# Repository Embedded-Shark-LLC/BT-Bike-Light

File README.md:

# BT-Bike-Light
Bluetooth-enabled bike light

## Hardware architecture diagram

## PCB Renders
|PCB Front|PCB Back|
|---------|--------|
|||

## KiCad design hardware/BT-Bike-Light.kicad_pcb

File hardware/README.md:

# Hardware

## Architecture diagram

## Major components
| Description           | Part Number           | Manufacturer          | Comments                          |
| --------------------- | --------------------- | --------------------- | --------------------------------- |
| Bluetooth module      | BT832                 | Fanstel               | 1.7-3.6 V, nRF52832               |
| Battery management IC | nPM1300               | Nordic Semiconductor  | 800 mA charge, onboard buck/LDO   |
| 24 GHz Radar module   | FEM11-F09             | Terasilic             | (not yet tested)                  |
| LED driver            | TPS92201              | Texas Instruments     | 2.5-5.5 V, 1.5 A                  |
| USB C port            | UJC-HP2-3-SMT-TR      | CUI Devices           | Power only, horizontal            |
| Red LED               | XPEBRD-L1-0000-00901  | Cree                  | 1.5 A, ~2.65 V @ 1.5 A            |
| Interface button      | PTS645VM31-2 LFS      | C&K                   | Right angle, THT                  |
| Buzzer                | SMT-0827-S-HT-R       | PUI Audio             | 2-5 V, 2.7 kHz, 85 dB @ 3.6V      |

## Minor components
| Description           | Part Number           | Manufacturer          | Comments                          |
| --------------------- | --------------------- | --------------------- | --------------------------------- |
| Fuse                  | TR/0603FA5-R          | Eaton                 | 5A rating, 35A breaking capacity  |
| Buzzer NMOS FET       | DMN3731U-7            | Diodes Incorporated   | Vgs < 1.8 V                       |
| 2.2 uH inductor (nPM) | WLFM201209M2R2PC      | Walson Technology     | 170 mR DCR, 0805                  |
| 2.2 uH inductor (LED) | SDER041H-2R2MS        | Cyntek                | 3.1A, 45mR DCR                    |

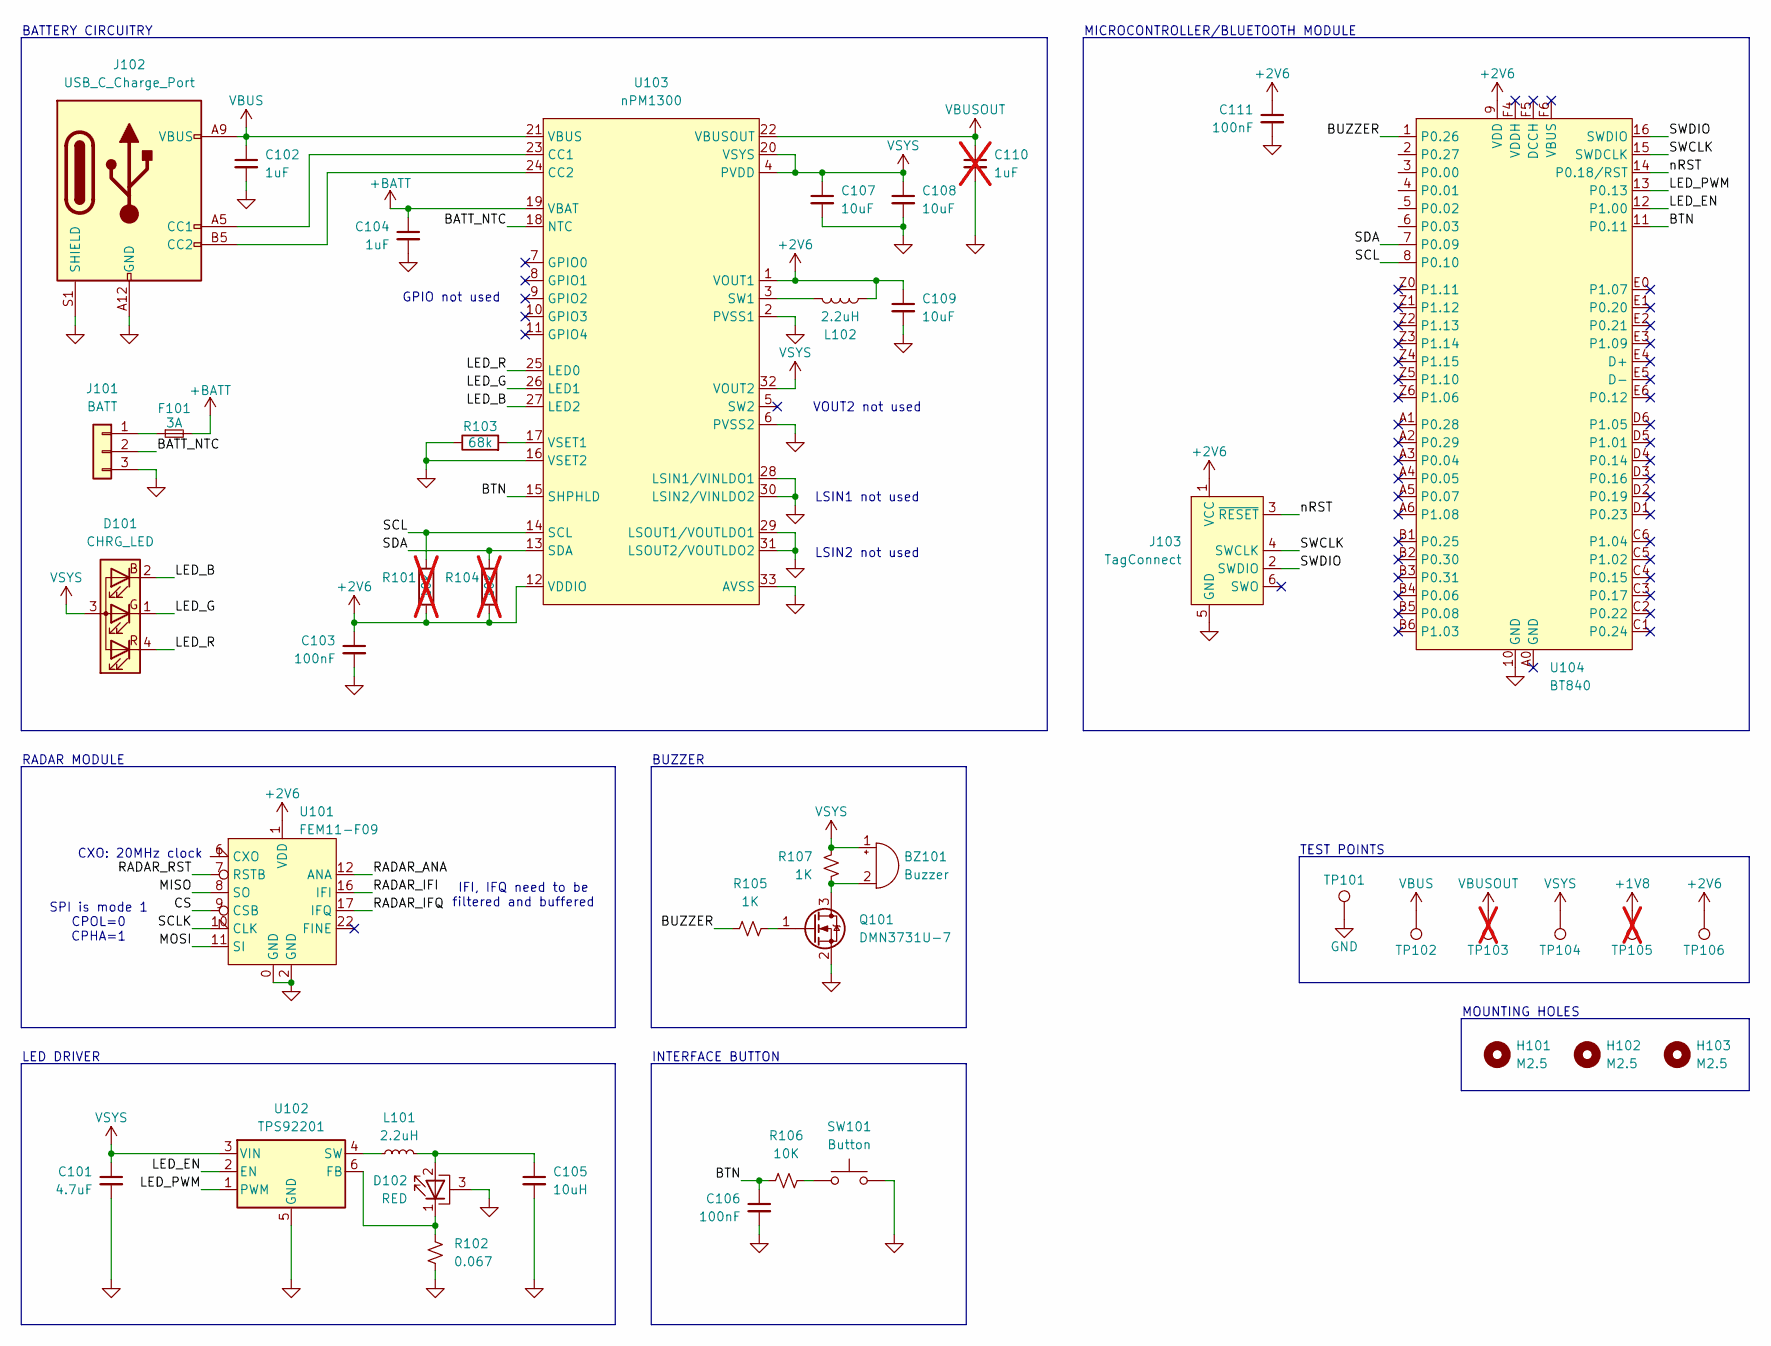
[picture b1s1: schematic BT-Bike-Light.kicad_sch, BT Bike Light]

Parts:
BZ101: Buzzer; SMT-0827-S-HT-R
C101: 4.7uF; C_0805_2012Metric_Pad1.18x1.45mm_HandSolder
C102, C104: 1uF; C_0805_2012Metric_Pad1.18x1.45mm_HandSolder
C103, C106, C111: 100nF; C_0805_2012Metric_Pad1.18x1.45mm_HandSolder
C105: 10uH; C_0805_2012Metric_Pad1.18x1.45mm_HandSolder
C107, C108, C109: 10uF; C_0805_2012Metric_Pad1.18x1.45mm_HandSolder
C110: 1uF; C_0805_2012Metric_Pad1.18x1.45mm_HandSolder; not fitted
D101: CHRG_LED; LED_0606
D102: RED; LED_Cree-XP
F101: 3A; Fuse_0603_1608Metric
H101, H102, H103: M2.5; MountingHole_2.7mm_M2.5
J101: BATT; JST_SH_SM03B-SRSS-TB_1x03-1MP_P1.00mm_Horizontal
J102: USB_C_Charge_Port; UJC-HP2-3-SMT-TR
J103: TagConnect; Tag-Connect_TC2030-IDC-NL_2x03_P1.27mm_Vertical
L101: 2.2uH; Inductor_3.6x4.1
L102: 2.2uH; L_0805_2012Metric
Q101: DMN3731U-7; SOT-23
R101, R104: 10k; R_0805_2012Metric_Pad1.20x1.40mm_HandSolder; not fitted
R102: 0.067; R_0805_2012Metric_Pad1.20x1.40mm_HandSolder
R103: 68k; R_0805_2012Metric_Pad1.20x1.40mm_HandSolder
R105, R107: 1K; R_0805_2012Metric_Pad1.20x1.40mm_HandSolder
R106: 10K; R_0805_2012Metric_Pad1.20x1.40mm_HandSolder
SW101: Button; SW_Tactile_SPST_Angled_PTS645Vx31-2LFS
TP101: GND; TestPoint_Pad_2.0x2.0mm
TP102: VBUS; TestPoint_Pad_2.0x2.0mm
TP103: VBUSOUT; TestPoint_Pad_2.0x2.0mm; not fitted
TP104: VSYS; TestPoint_Pad_2.0x2.0mm
TP105: 1V8; TestPoint_Pad_2.0x2.0mm; not fitted
TP106: 2V6; TestPoint_Pad_2.0x2.0mm
U101: FEM11-F09
U102: TPS92201; WSON-6-1EP_2x2mm_P0.65mm_EP1x1.6mm_ThermalVias
U103: nPM1300; QFN-32-1EP_5x5mm_P0.5mm_EP3.45x3.45mm_ThermalVias
U104: BT840

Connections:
+2V6: C103.1, C109.1, C111.1, J103.1 (VCC), L102.2, R101.2, R104.2, TP106.1, U101.1 (VDD), U101.14 (VDD), U101.19 (VDD), U103.1 (VOUT1), U103.12 (VDDIO), U104.9 (VDD)
+BATT: C104.1, F101.2, U103.19 (VBAT)
/BATT_NTC: J101.2, U103.18 (NTC)
/BTN: C106.1, R106.1, U103.15 (SHPHLD), U104.11 (P0.11)
/BUZZER: R105.1, U104.1 (P0.26)
/CS: U101.9 (CSB)
/LED_B: D101.2 (BK), U103.27 (LED2)
/LED_EN: U102.2 (EN), U104.12 (P1.00)
/LED_G: D101.1 (GK), U103.26 (LED1)
/LED_PWM: U102.1 (PWM), U104.13 (P0.13)
/LED_R: D101.4 (RK), U103.25 (LED0)
/MISO: U101.8 (SO)
/MOSI: U101.11 (SI)
/RADAR_ANA: U101.12 (ANA)
/RADAR_IFI: U101.16 (IFI)
/RADAR_IFQ: U101.17 (IFQ)
/RADAR_RST: U101.7 (RSTB)
/SCL: R101.1, U103.14 (SCL), U104.8 (P0.10)
/SCLK: U101.10 (CLK)
/SDA: R104.1, U103.13 (SDA), U104.7 (P0.09)
/SWCLK: J103.4 (SWCLK), U104.15 (SWDCLK)
/SWDIO: J103.2 (SWDIO), U104.16 (SWDIO)
/nRST: J103.3 (~RESET), U104.14 (P0.18/RST)
unnamed: BZ101.2 (-), Q101.3 (D), R107.2
unnamed: C105.1, D102.2 (A), L101.2
unnamed: D102.1 (K), R102.2, U102.6 (FB)
unnamed: F101.1, J101.1
unnamed: J102.A5 (CC1), U103.23 (CC1)
unnamed: J102.B5 (CC2), U103.24 (CC2)
unnamed: Q101.1 (G), R105.2
unnamed: R106.2, SW101.2
unnamed: L101.1, U102.4 (SW)
unnamed: L102.1, U103.3 (SW1)
unnamed: R103.2, U103.17 (VSET1)
VBUS: C102.1, J102.A9 (VBUS), J102.B9 (VBUS), TP102.1, U103.21 (VBUS)
VBUSOUT: C110.1, TP103.1, U103.22 (VBUSOUT)
VSYS: BZ101.1 (+), C101.1, C107.1, C108.1, D101.3 (A), R107.1, TP104.1, U102.3 (VIN), U103.4 (PVDD), U103.20 (VSYS), U103.32 (VOUT2)

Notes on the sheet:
CXO: 20MHz clock
LSIN1 not used
INTERFACE BUTTON
MOUNTING HOLES
TEST POINTS
GPIO not used
IFI, IFQ need to be filtered and buffered
BATTERY CIRCUITRY
BUZZER
VOUT2 not used
LSIN2 not used
RADAR MODULE
MICROCONTROLLER/BLUETOOTH MODULE
LED DRIVER
SPI is mode 1 CPOL=0 CPHA=1

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
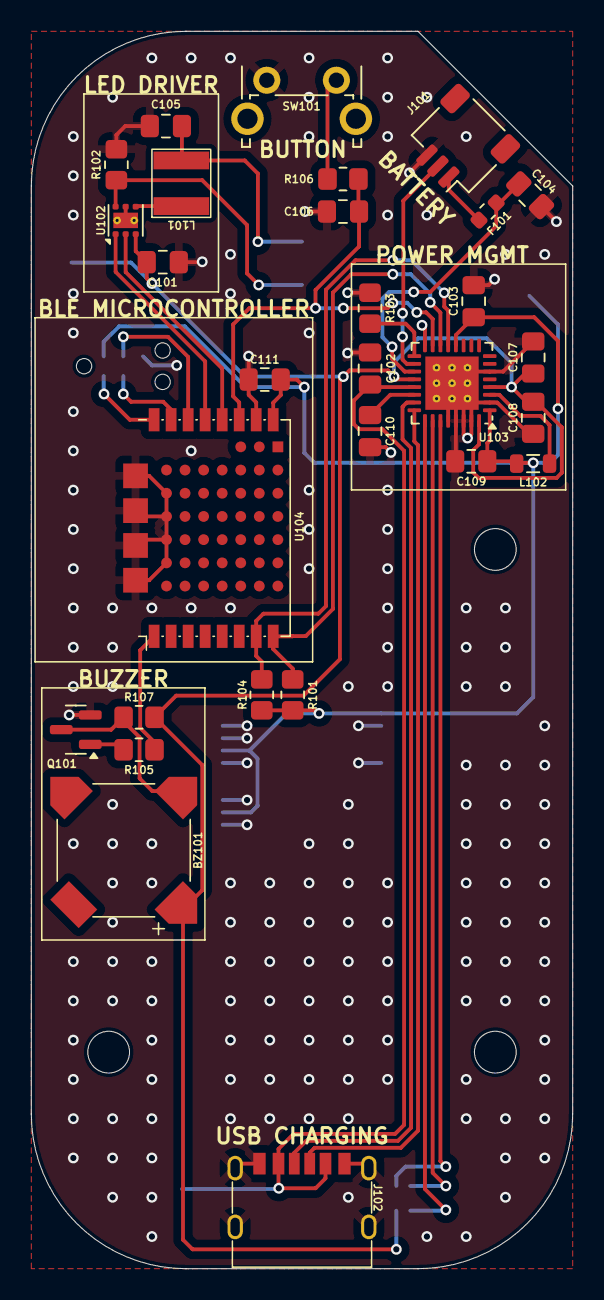
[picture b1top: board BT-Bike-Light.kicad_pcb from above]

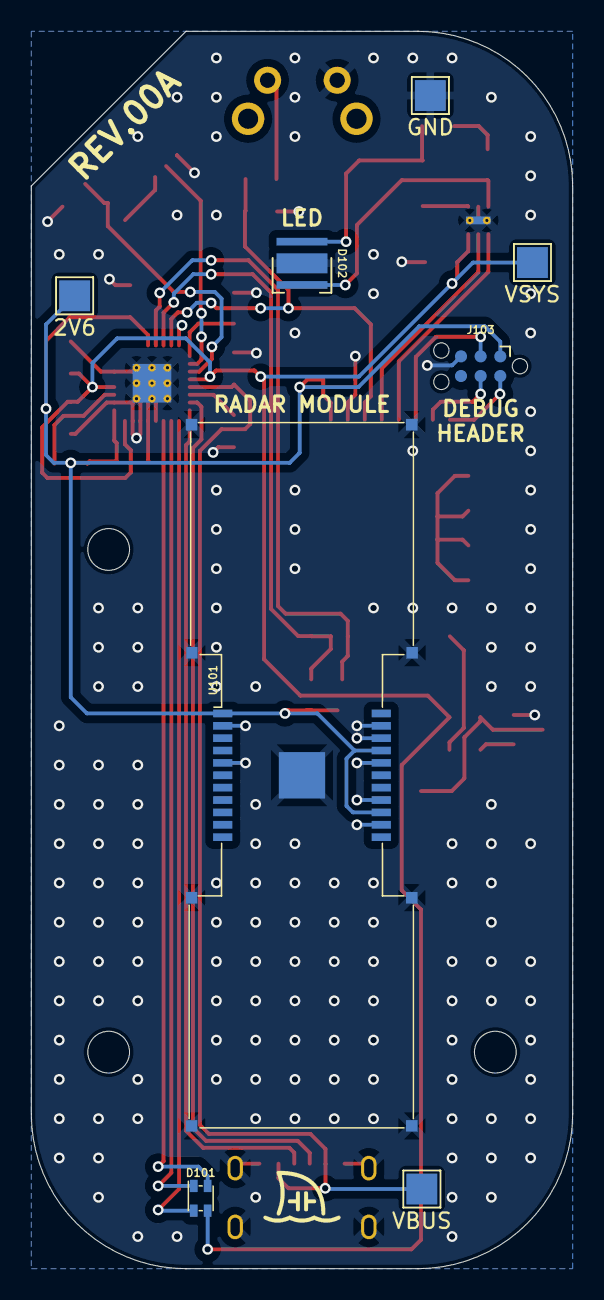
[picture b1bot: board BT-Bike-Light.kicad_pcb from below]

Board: 4 copper layers, 35.0 x 80.0 mm, 40 parts (8 on the bottom side), 30 nets.

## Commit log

2024-08-24 Ignore KiCad lock files
2024-08-24 Add BC805M
2024-08-24 Add XPE2 LED
2024-08-24 Add README
2024-08-24 Update folder structure
2024-08-24 Ignore draw.io temporary files
2024-08-24 Add debug connector
2024-08-24 Add accelerometer
2024-08-24 Add LED driver
2024-08-24 Update part numbers
2024-08-24 Add hardware architecture diagram
2024-08-24 Add datesheets
2024-08-24 Update naming convention
2024-08-24 Add USB/UART bridge
2024-08-24 Add USB-C receptacle
2024-08-24 Add button
2024-08-24 Add buzzer
2024-08-24 Add battery protection IC
2024-08-24 Remove USB/UART bridge
2024-08-24 Add battery charger
2024-08-24 Add LDO
2024-08-24 Add battery connector
2024-08-24 Update battery connector
2024-08-24 Update USB-C receptacle
2024-08-24 Add supporting electronics for LDO
2024-08-24 Finish wiring SWD header
2024-08-24 Add supporting electronics for battery charger
2024-08-24 Add supporting electronics for battery protection IC
2024-08-24 Add supporting electronics to USB-C receptacle
2024-08-24 Add supporting electronics for LED driver
2024-08-24 Add supporting electronics for button
2024-08-24 Add supporting electronics for buzzer
2024-08-25 Add supporting electronics for accelerometer
2024-08-25 Replace battery protection IC
2024-08-25 Add battery monitor datasheet
2024-08-25 Add resettable fuse
2024-08-25 Clean up schematic
2024-08-25 Schematic cleanup
2024-08-25 Remove unused dual NMOS
2024-08-25 Assign footprints
2024-08-25 Split schematic into multiple sheets
2024-08-25 Replace battery connector footprint and import footprints
2024-08-25 Add battery protection and swap some connectors
2024-08-26 Finish pin assignments
2024-08-31 Remove accelerometer, replace battery stuff with nPM1300
2024-08-31 Add datasheet
2024-08-31 Place components
2024-08-31 Update buzzer
2024-08-31 Clean up PCB
2024-08-31 Remove unused library
2024-08-31 Use submodule for libraries
2024-08-31 Change library paths
2024-08-31 Update submodule
2024-08-31 Remove old schematic pages
2024-08-31 Route components
2024-08-31 Update libraries
2024-08-31 Battery polarity toggle #2
2024-08-31 Reset button #1
2024-08-31 Add via stitching
2024-09-14 Shrink PCB design
2024-09-14 Update dates
2024-09-15 Create LICENSE
2024-10-05 Add accelerometer, replace LED driver, add internal GND layers, fix VSYS routing, update datasheets
2024-10-05 Update libs
2024-10-05 PCB cleanup
2024-10-05 DRC exclusion for silkscreen clipping edge of PCB
2024-10-20 PWM test
2024-10-20 Add PWM code
2024-10-20 Update board location
2024-10-20 Add LED driver enable signal
2024-10-20 Add LED patterns and separate LED logic
2024-10-20 Code cleanup
2024-10-21 Add button to toggle pattern and shut off light
2024-10-21 Pattern change logic
2024-10-21 Add long-press wakeup logic
2024-10-21 Separate power off logic
2024-10-21 Add debounce logic
2024-10-22 Add I2C config and read device ID from accelerometer
2024-10-24 Clean up I2C read/write register functions
2024-10-25 Sleep/wake interrupts partially working
2024-10-26 Add accelerometer initialization and helper functions
2024-10-26 Update function declarations
2024-10-26 Use thread to poll button
2024-10-26 Rename sys function calls to device
2024-10-26 Don't shut off accelerometer when powering off device (need wakeup interrupt)
2024-10-26 Add function headers
2024-10-26 Remove acclerometer
2024-10-26 Remove I2C bus and accelerometer pin definitions
2024-10-26 Remove accelerometer
2024-11-02 Switch to BT840 (waiting on feedback from radar module supplier before additional changes)
2024-11-17 Add radar module to schematic (partially wired)
2024-11-18 New battery connector and board outline
2024-11-19 Increase passive component sizes
2024-11-19 Battery management IC component placement
2024-11-19 Component placement
2024-11-20 Route board
2024-11-20 Update hardware block diagram
2024-11-20 Update component list
2024-11-20 Update board renders
2024-11-23 Combine 1V8 and 2V6 line to 2V6
2024-11-23 Update documentation
2024-11-23 Schematic cleanup and add test points
2024-11-23 Schematic and PCB cleanup
